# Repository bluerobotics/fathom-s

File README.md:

# Fathom-S

The Fathom Tether Boards are part of Blue Robotics' *Fathom Tether*. These boards provide interfaces and functionality for the communication methods used with the tether. With the Fathom tether, it is quick and easy to get up and running and interface with your ROV or other application.

The schematic and board layout are designed in EagleCAD.

Please see the [Blue Robotics Fathom-S Documentation Page](http://docs.bluerobotics.com/fathom-s/) for more information.

## License

The Fathom Serial Hardware Design is released under the MIT License.

## Revision History

0.0 - Under development. Not fully functional.

0.1 - Second prototype. Not fully functional.

0.2 - Third prototype. First beta release - works great.

0.3 - Rev5, incorporating big changes from beta tests.

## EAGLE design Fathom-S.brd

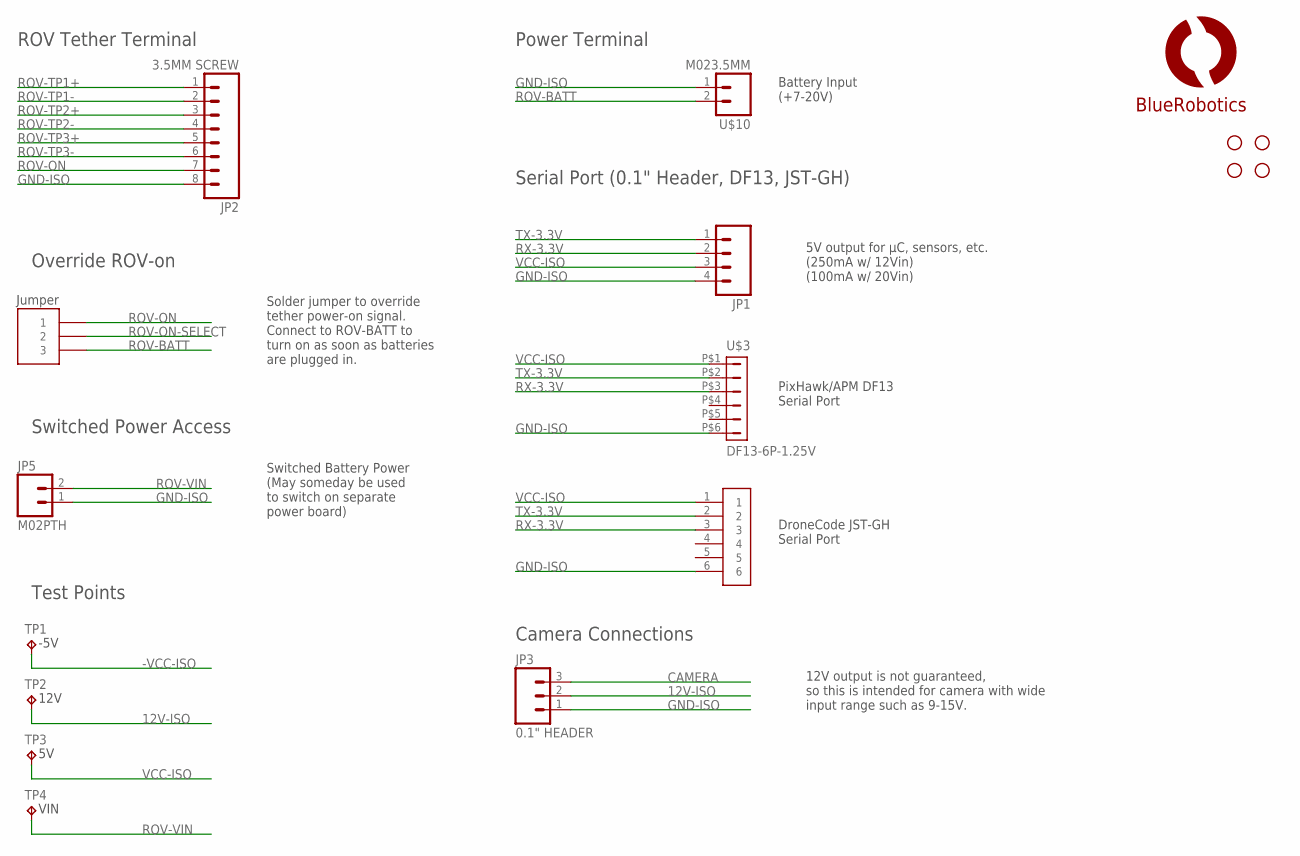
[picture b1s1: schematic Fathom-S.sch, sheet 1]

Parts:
JP1: M04PTH; 1X04
JP2: 3.5MM SCREW; SCREWTERMINAL-3.5MM-8
JP3: 0.1" HEADER; 1X03
JP5: M02PTH; 1X02
STANDOFF1, STANDOFF2, STANDOFF3, STANDOFF4: STAND-OFF
TP1: -5V; B1,27
TP2: 12V; B1,27
TP3: 5V; B1,27
TP4: VIN; B1,27
U$3: DF13-6P-1.25V; DF13C-6P-1.25V
U$4: LOGOFULL-M; BR-FULL-LOGO-MEDIUM
U$10: M023.5MM; SCREWTERMINAL-3.5MM-2
U$11: JST-GH-6TOP-ENTRY; JST-GH-TOP-6
U$13: HEADER-33MM; HEADER-2MM-3POS

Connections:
12V-ISO: JP3.2, TP2.TP; also elsewhere on the board
-VCC-ISO: TP1.TP; also elsewhere on the board
CAMERA: JP3.3; also elsewhere on the board
GND-ISO: JP1.4, JP2.8, JP3.1, JP5.1, U$3.P$6 (6), U$10.1, U$11.6; also elsewhere on the board
ROV-BATT: U$10.2, U$13.P$3 (3); also elsewhere on the board
ROV-ON: JP2.7, U$13.P$1 (1)
ROV-ON-SELECT: U$13.P$2 (2); also elsewhere on the board
ROV-TP1+: JP2.1; also elsewhere on the board
ROV-TP1-: JP2.2; also elsewhere on the board
ROV-TP2+: JP2.3; also elsewhere on the board
ROV-TP2-: JP2.4; also elsewhere on the board
ROV-TP3+: JP2.5; also elsewhere on the board
ROV-TP3-: JP2.6; also elsewhere on the board
ROV-VIN: JP5.2, TP4.TP; also elsewhere on the board
RX-3.3V: JP1.2, U$3.P$3 (3), U$11.3; also elsewhere on the board
TX-3.3V: JP1.1, U$3.P$2 (2), U$11.2; also elsewhere on the board
VCC-ISO: JP1.3, TP3.TP, U$3.P$1 (1), U$11.1; also elsewhere on the board

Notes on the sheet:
ROV Tether Terminal
Power Terminal
Camera Connections
Serial Port (0.1" Header, DF13, JST-GH)
Solder jumper to override tether power-on signal. Connect to ROV-BATT to turn on as soon as batteries are plugged in.
Override ROV-on
Battery Input (+7-20V)
5V output for µC, sensors, etc. (250mA w/ 12Vin) (100mA w/ 20Vin)
12V output is not guaranteed, so this is intended for camera with wide input range such as 9-15V.
Jumper
DroneCode JST-GH Serial Port
PixHawk/APM DF13 Serial Port
Switched Battery Power (May someday be used to switch on separate power board)
Switched Power Access
Test Points

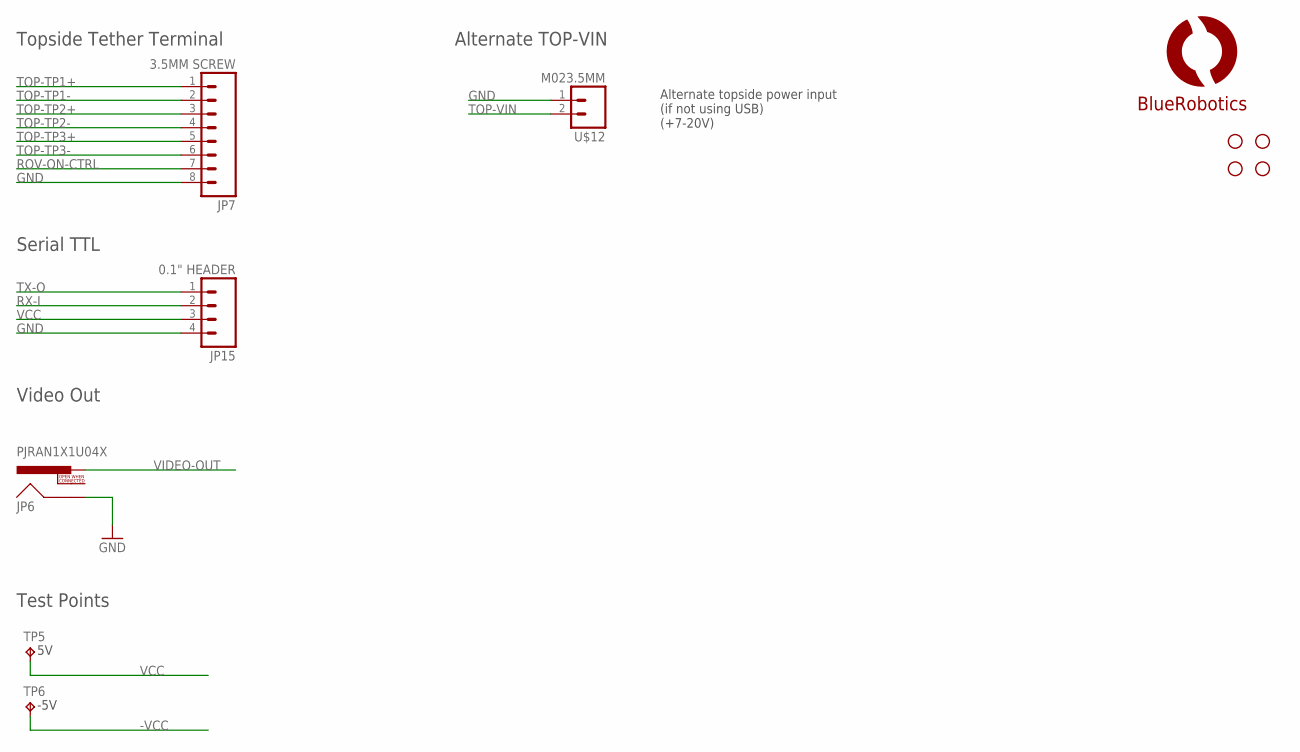
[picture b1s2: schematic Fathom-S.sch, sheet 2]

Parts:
JP6: PJRAN1X1U04X; RCA
JP7: 3.5MM SCREW; SCREWTERMINAL-3.5MM-8
JP15: 0.1" HEADER; 1X04
STANDOFF5, STANDOFF6, STANDOFF7, STANDOFF8: STAND-OFF
TP5: 5V; B1,27
TP6: -5V; B1,27
U$5: LOGOBR-LOGO-MS-COPPER; BR-LOGO-MEDIUM-SMALL-COPPER
U$12: M023.5MM; SCREWTERMINAL-3.5MM-2

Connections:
-VCC: TP6.TP; also elsewhere on the board
GND: JP6.SHELL, JP7.8, JP15.4, U$12.1; also elsewhere on the board
ROV-ON-CTRL: JP7.7; also elsewhere on the board
RX-I: JP15.2; also elsewhere on the board
TOP-TP1+: JP7.1; also elsewhere on the board
TOP-TP1-: JP7.2; also elsewhere on the board
TOP-TP2+: JP7.3; also elsewhere on the board
TOP-TP2-: JP7.4; also elsewhere on the board
TOP-TP3+: JP7.5; also elsewhere on the board
TOP-TP3-: JP7.6; also elsewhere on the board
TOP-VIN: U$12.2; also elsewhere on the board
TX-O: JP15.1; also elsewhere on the board
VCC: JP15.3, TP5.TP; also elsewhere on the board
VIDEO-OUT: JP6.PIN; also elsewhere on the board

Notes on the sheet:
Topside Tether Terminal
Alternate TOP-VIN
Video Out
Serial TTL
Alternate topside power input (if not using USB) (+7-20V)
Test Points

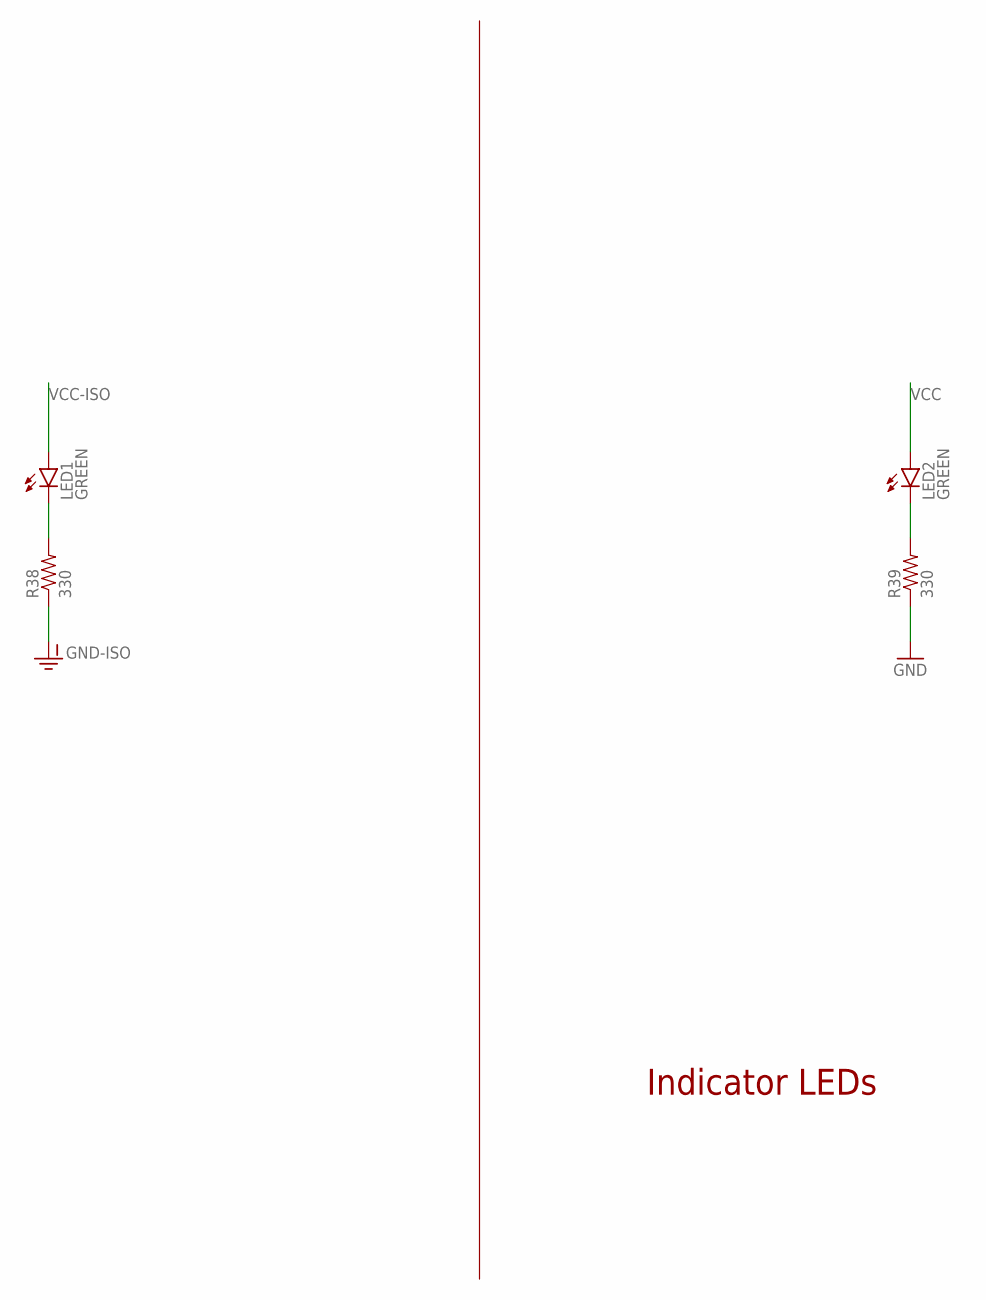
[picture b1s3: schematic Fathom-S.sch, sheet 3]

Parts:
LED1, LED2: GREEN; LED-0603
R38, R39: 330; 0603-RES

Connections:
GND: R39.1; also elsewhere on the board
GND-ISO: R38.1; also elsewhere on the board
unnamed: LED1.C, R38.2
unnamed: LED2.C, R39.2
VCC: LED2.A; also elsewhere on the board
VCC-ISO: LED1.A; also elsewhere on the board

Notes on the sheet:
Indicator LEDs

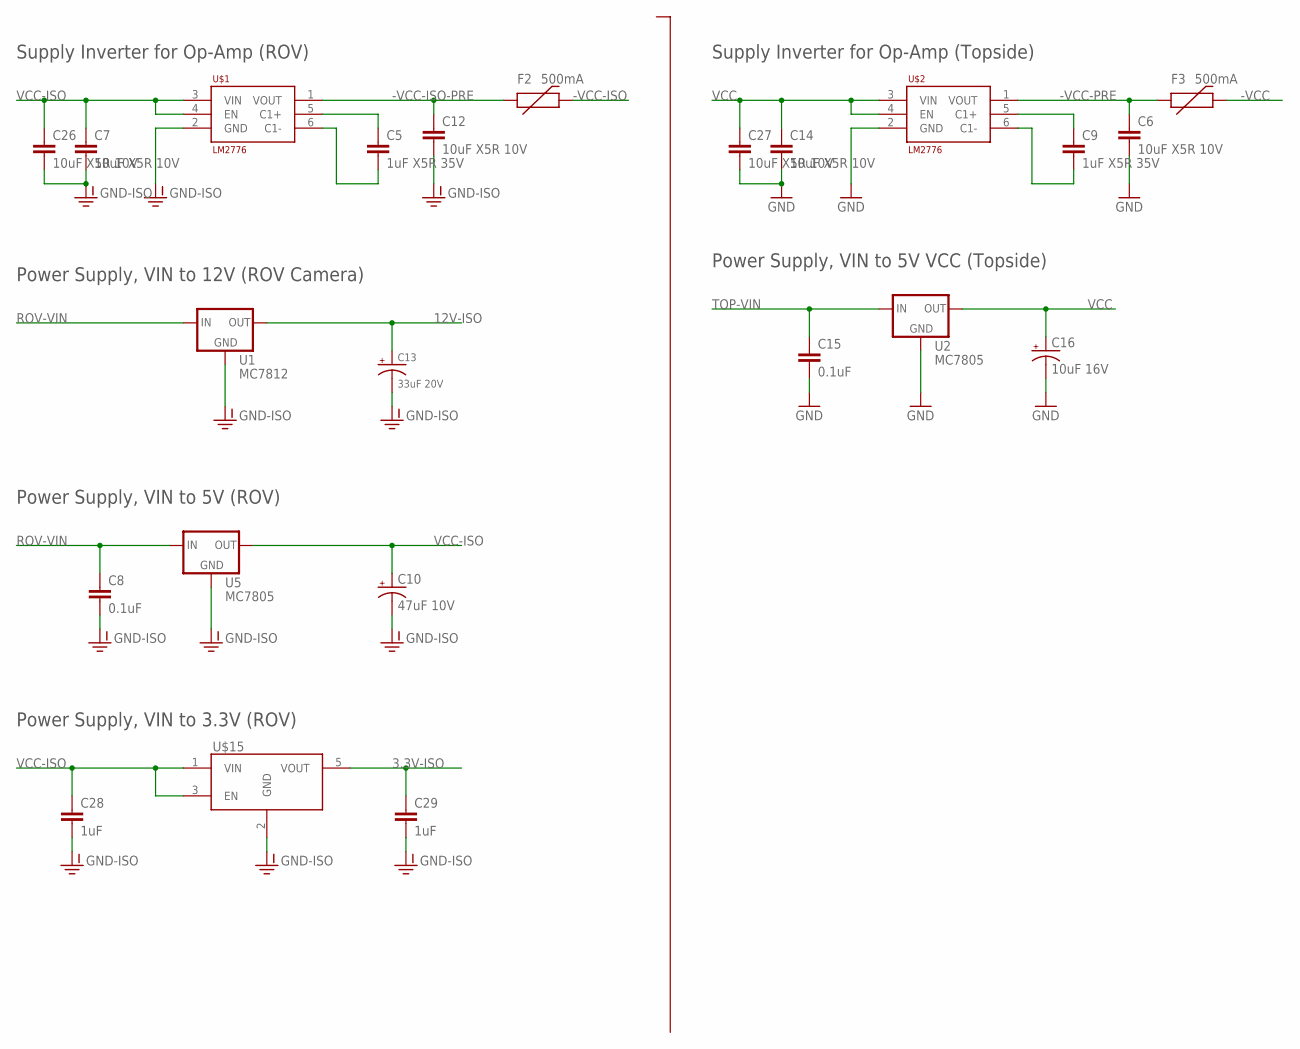
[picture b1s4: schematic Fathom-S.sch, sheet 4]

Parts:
C5, C9: 1uF X5R 35V; 0603-CAP
C6, C7, C12, C14, C26, C27: 10uF X5R 10V; 0805
C8, C15: 0.1uF; 0603-CAP
C10: 47uF 10V; EIA3528
C13: 33uF 20V; C2413
C16: 10uF 16V; EIA3216
C28, C29: 1uF; 0603-CAP
F2, F3: 500mA; 0603
U1: MC7812; DPAK
U2, U5: MC7805; DPAK
U$1, U$2: LM2776; SOT-23-6
U$15: VREG-MIC5365; SC70-5L

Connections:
3.3V-ISO: C29.1, U$15.5 (VOUT); also elsewhere on the board
12V-ISO: C13.+, U1.3 (OUT); also elsewhere on the board
-VCC: F3.2; also elsewhere on the board
-VCC-ISO: F2.2; also elsewhere on the board
-VCC-ISO-PRE: C12.1, F2.1, U$1.1 (VOUT)
-VCC-PRE: C6.1, F3.1, U$2.1 (VOUT)
GND: C6.2, C14.2, C15.2, C16.C (-), C27.2, U2.4 (GND), U$2.2 (GND); also elsewhere on the board
GND-ISO: C7.2, C8.2, C10.C (-), C12.2, C13.-, C26.2, C28.2, C29.2, U1.4 (GND), U5.4 (GND), U$1.2 (GND), U$15.2 (GND); also elsewhere on the board
unnamed: C9.1, U$2.5 (C1+)
unnamed: C9.2, U$2.6 (C1-)
unnamed: C5.1, U$1.5 (C1+)
unnamed: C5.2, U$1.6 (C1-)
ROV-VIN: C8.1, U1.1 (IN), U5.1 (IN); also elsewhere on the board
TOP-VIN: C15.1, U2.1 (IN); also elsewhere on the board
VCC: C14.1, C16.A (+), C27.1, U2.3 (OUT), U$2.3 (VIN), U$2.4 (EN); also elsewhere on the board
VCC-ISO: C7.1, C10.A (+), C26.1, C28.1, U5.3 (OUT), U$1.3 (VIN), U$1.4 (EN), U$15.1 (VIN), U$15.3 (EN); also elsewhere on the board

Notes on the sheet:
Supply Inverter for Op-Amp (ROV)
Supply Inverter for Op-Amp (Topside)
Power Supply, VIN to 12V (ROV Camera)
Power Supply, VIN to 5V (ROV)
Power Supply, VIN to 5V VCC (Topside)
Power Supply, VIN to 3.3V (ROV)

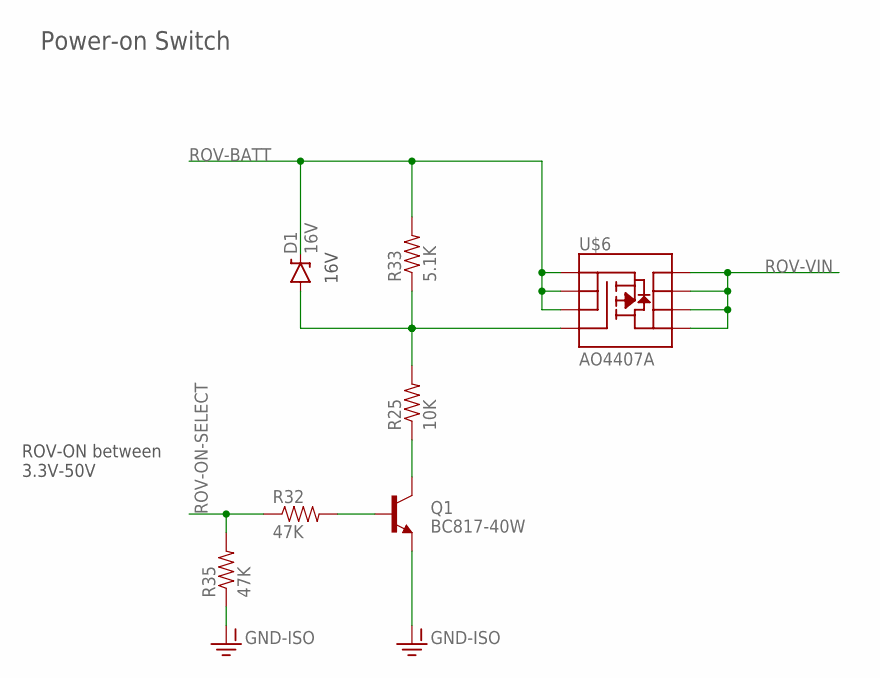
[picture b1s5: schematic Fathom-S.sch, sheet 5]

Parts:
D1: 16V; SOD-323
Q1: BC817-40W; SOT23
R25: 10K; 0603-RES
R32, R35: 47K; 0603-RES
R33: 5.1K; 0603-RES
U$6: AO4407A; SO08

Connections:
GND-ISO: Q1.2 (E), R35.1; also elsewhere on the board
unnamed: Q1.1 (B), R32.2
unnamed: D1.A, R25.2, R33.1, U$6.4 (G)
unnamed: Q1.3 (C), R25.1
ROV-BATT: D1.C, R33.2, U$6.1 (S), U$6.2 (S), U$6.3 (S); also elsewhere on the board
ROV-ON-SELECT: R32.1, R35.2; also elsewhere on the board
ROV-VIN: U$6.5 (D), U$6.6 (D), U$6.7 (D), U$6.8 (D); also elsewhere on the board

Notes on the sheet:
Power-on Switch
ROV-ON between 3.3V-50V
16V

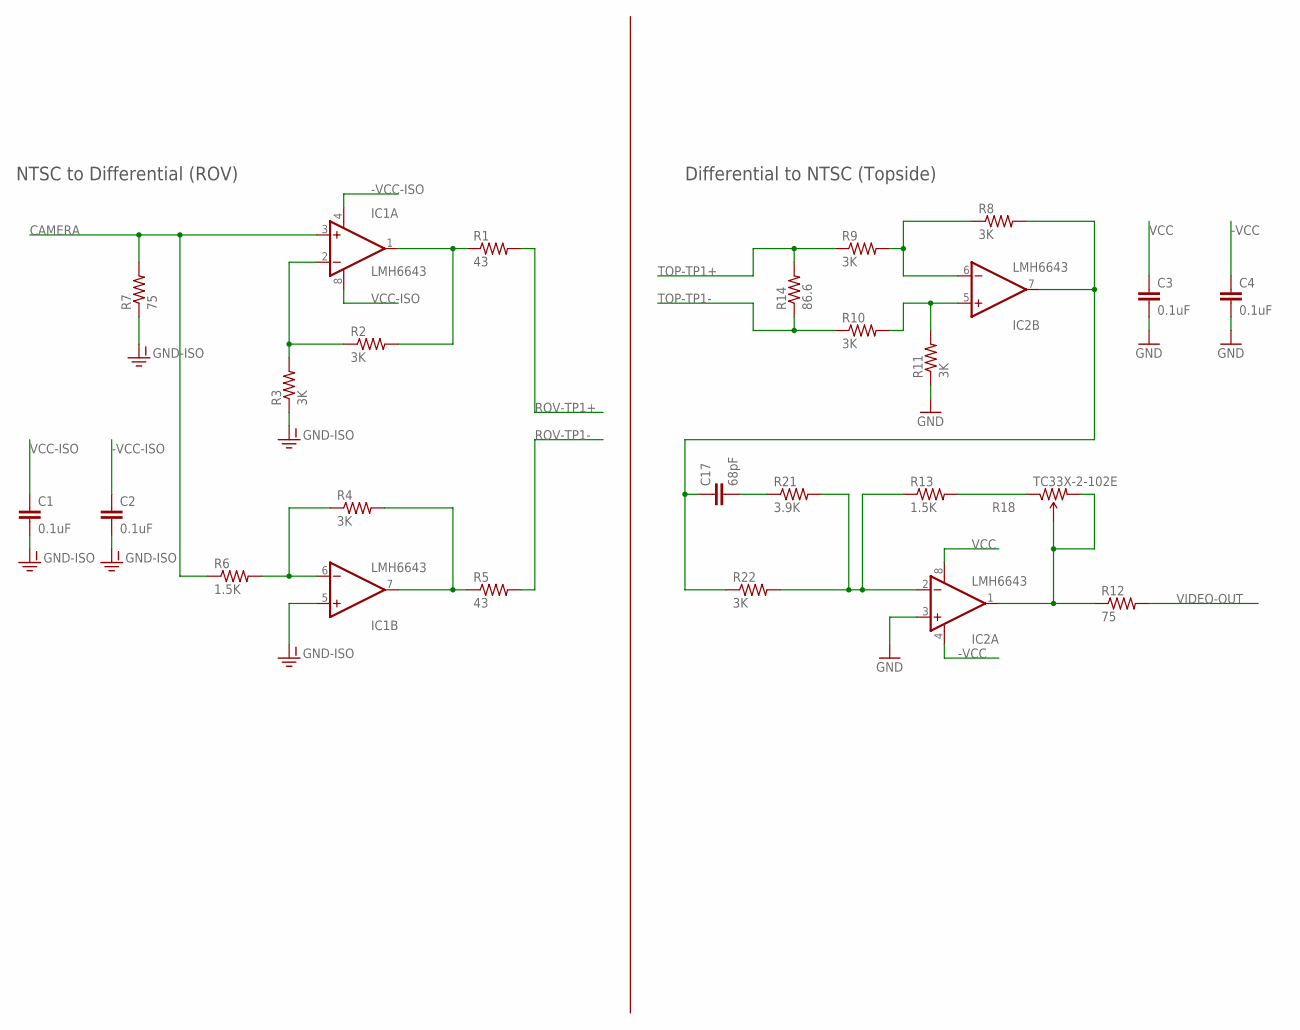
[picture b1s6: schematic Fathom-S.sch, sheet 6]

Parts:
C1, C2, C3, C4: 0.1uF; 0603-CAP
C17: 68pF; 0603-CAP
IC1, IC2: LMH6643; MSOP8
R1, R5: 43; 0603-RES
R2, R3, R4, R8, R9, R10, R11, R22: 3K; 0603-RES
R6, R13: 1.5K; 0603-RES
R7, R12: 75; 0603-RES
R14: 86.6; 0603-RES
R18: TC33X-2-102E; TRIMPOT_TC33
R21: 3.9K; 0603-RES

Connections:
-VCC: C4.1, IC2.4 (V-); also elsewhere on the board
-VCC-ISO: C2.1, IC1.4 (V-); also elsewhere on the board
CAMERA: IC1.3 (+IN), R6.1, R7.2; also elsewhere on the board
GND: C3.2, C4.2, IC2.3 (+IN), R11.1; also elsewhere on the board
GND-ISO: C1.2, C2.2, IC1.5 (+IN), R3.1, R7.1; also elsewhere on the board
unnamed: IC1.1 (OUT), R1.1, R2.2
unnamed: IC1.7 (OUT), R4.2, R5.1
unnamed: IC1.2 (-IN), R2.1, R3.2
unnamed: IC1.6 (-IN), R4.1, R6.2
unnamed: IC2.5 (+IN), R10.2, R11.2
unnamed: IC2.6 (-IN), R8.1, R9.2
unnamed: R13.2, R18.1 (CCW)
unnamed: C17.1, IC2.7 (OUT), R8.2, R22.1
unnamed: IC2.2 (-IN), R13.1, R21.2, R22.2
unnamed: C17.2, R21.1
unnamed: IC2.1 (OUT), R12.1, R18.2 (WIPER), R18.3 (CW)
ROV-TP1+: R1.2; also elsewhere on the board
ROV-TP1-: R5.2; also elsewhere on the board
TOP-TP1+: R9.1, R14.2; also elsewhere on the board
TOP-TP1-: R10.1, R14.1; also elsewhere on the board
VCC: C3.1, IC2.8 (V+); also elsewhere on the board
VCC-ISO: C1.1, IC1.8 (V+); also elsewhere on the board
VIDEO-OUT: R12.2; also elsewhere on the board

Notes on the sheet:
NTSC to Differential (ROV)
Differential to NTSC (Topside)

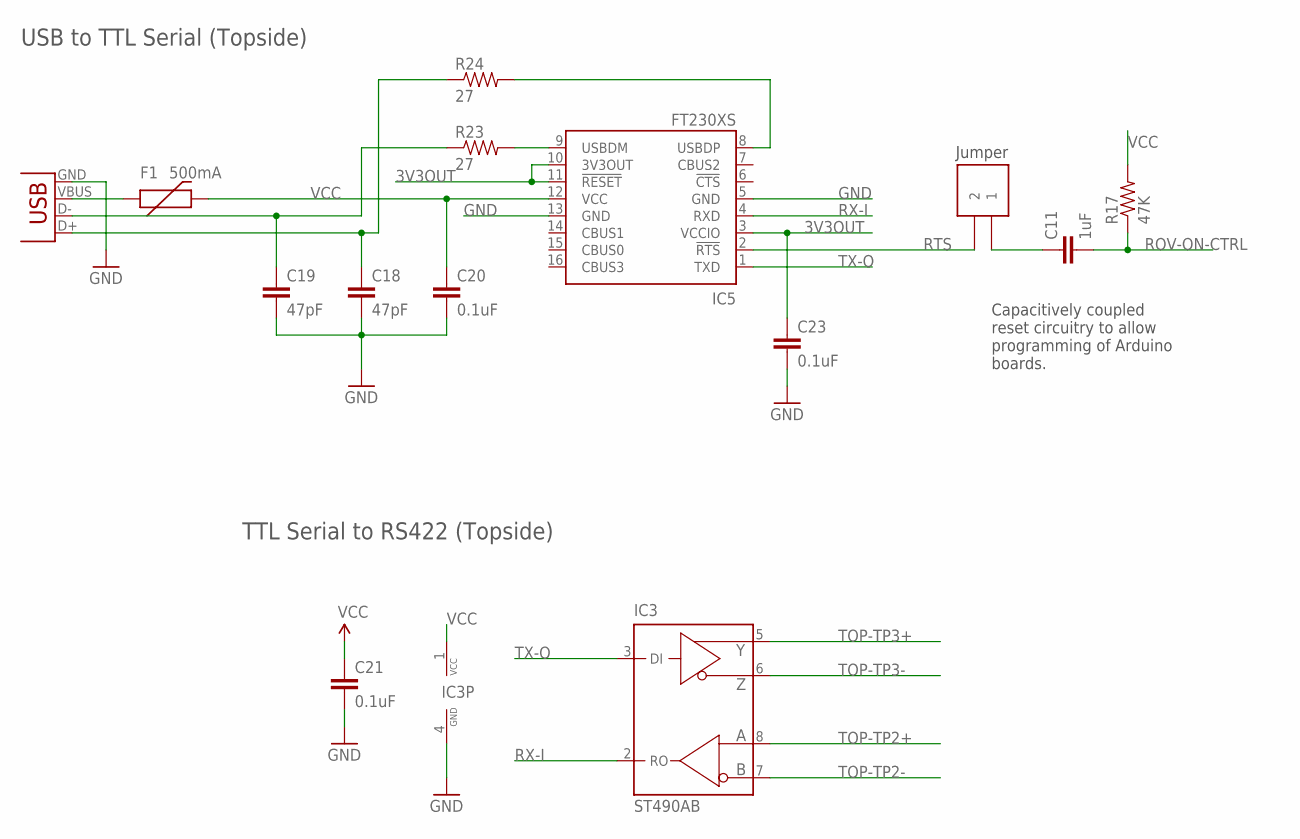
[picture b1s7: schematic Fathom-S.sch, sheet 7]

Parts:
C11: 1uF; 0603-CAP
C18, C19: 47pF; 0603-CAP
C20, C21, C23: 0.1uF; 0603-CAP
F1: 500mA; 0603
IC3: ST490AB; SO08
IC5: FT230XS; SSOP16
R17: 47K; 0603-RES
R23, R24: 27; 0603-RES
U$16: HEADER-22MM; HEADER-2MM-2POS
X2: USBSMD; USB-MINIB

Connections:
3V3OUT: C23.1, IC5.3 (VCCIO), IC5.10 (3V3OUT), IC5.11 (!RESET)
GND: C18.2, C19.2, C20.2, C21.2, C23.2, IC3.4 (GND), IC5.5 (GND), IC5.13 (GND), X2.GND; also elsewhere on the board
unnamed: C11.1, U$16.P$1 (1)
unnamed: C19.1, R23.1, X2.D-
unnamed: C18.1, R24.1, X2.D+
unnamed: F1.1, X2.VBUS
unnamed: IC5.8 (USBDP), R24.2
unnamed: IC5.9 (USBDM), R23.2
ROV-ON-CTRL: C11.2, R17.1; also elsewhere on the board
RTS: IC5.2 (!RTS), U$16.P$2 (2)
RX-I: IC3.2 (RO), IC5.4 (RXD); also elsewhere on the board
TOP-TP2+: IC3.8 (A); also elsewhere on the board
TOP-TP2-: IC3.7 (B); also elsewhere on the board
TOP-TP3+: IC3.5 (Y); also elsewhere on the board
TOP-TP3-: IC3.6 (Z); also elsewhere on the board
TX-O: IC3.3 (DI), IC5.1 (TXD); also elsewhere on the board
VCC: C20.1, C21.1, F1.2, IC3.1 (VCC), IC5.12 (VCC), R17.2; also elsewhere on the board

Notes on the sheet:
USB to TTL Serial (Topside)
TTL Serial to RS422 (Topside)
Capacitively coupled reset circuitry to allow programming of Arduino boards.
Jumper

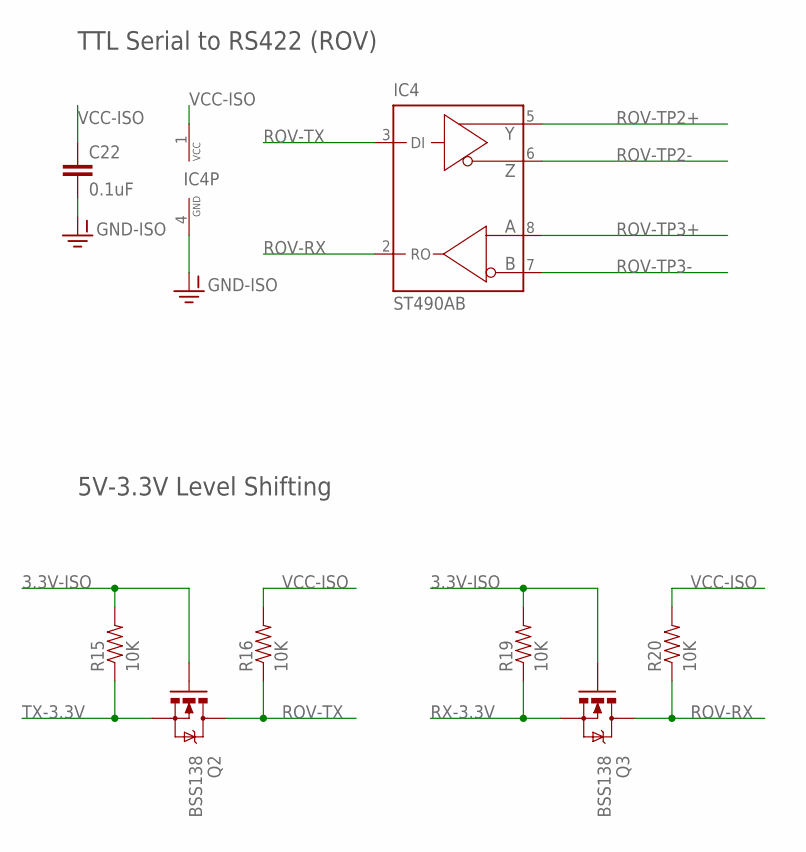
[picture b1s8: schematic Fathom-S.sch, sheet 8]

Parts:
C22: 0.1uF; 0603-CAP
IC4: ST490AB; SO08
Q2, Q3: BSS138; SOT23
R15, R16, R19, R20: 10K; 0603-RES

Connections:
3.3V-ISO: Q2.1 (G), Q3.1 (G), R15.2, R19.2; also elsewhere on the board
GND-ISO: C22.2, IC4.4 (GND); also elsewhere on the board
ROV-RX: IC4.2 (RO), Q3.3 (D), R20.1
ROV-TP2+: IC4.5 (Y); also elsewhere on the board
ROV-TP2-: IC4.6 (Z); also elsewhere on the board
ROV-TP3+: IC4.8 (A); also elsewhere on the board
ROV-TP3-: IC4.7 (B); also elsewhere on the board
ROV-TX: IC4.3 (DI), Q2.3 (D), R16.1
RX-3.3V: Q3.2 (S), R19.1; also elsewhere on the board
TX-3.3V: Q2.2 (S), R15.1; also elsewhere on the board
VCC-ISO: C22.1, IC4.1 (VCC), R16.2, R20.2; also elsewhere on the board

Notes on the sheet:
TTL Serial to RS422 (ROV)
5V-3.3V Level Shifting

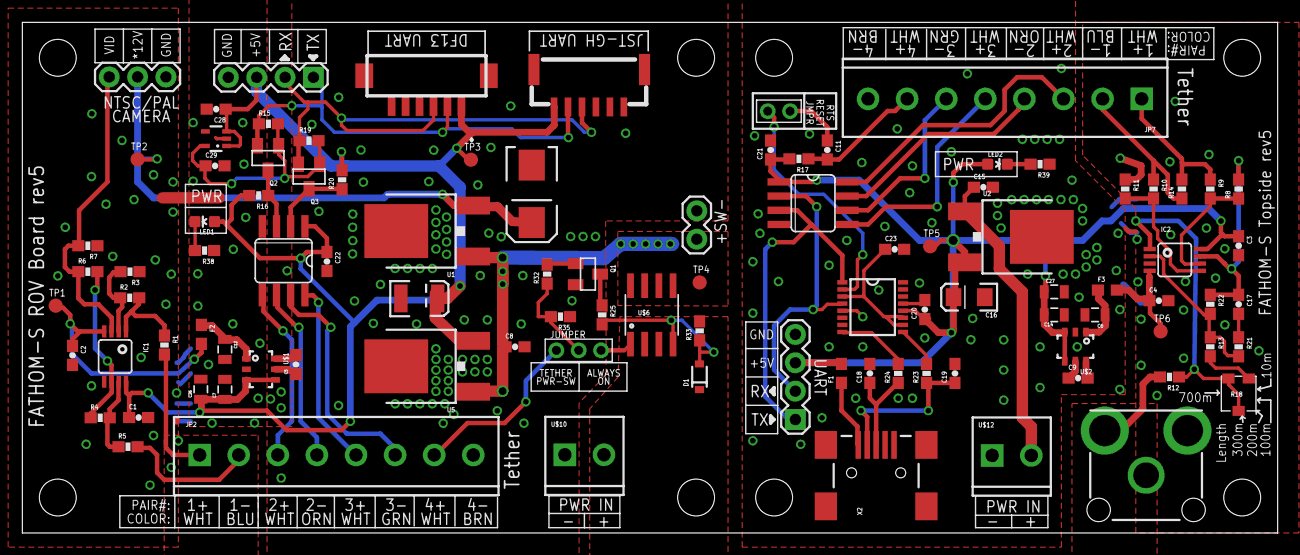
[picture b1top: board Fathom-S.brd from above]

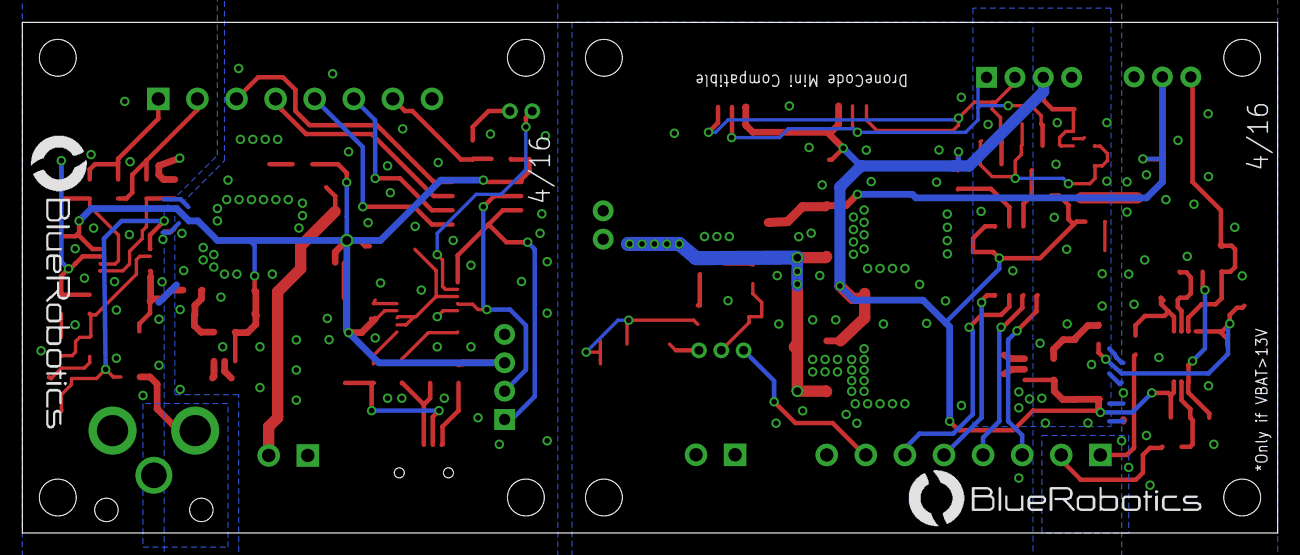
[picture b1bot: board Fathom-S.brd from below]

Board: 2 copper layers, 112.4 x 45.7 mm, 110 parts (2 on the bottom side), 64 nets.

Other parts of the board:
U$7: LOGOFULL-M; BR-FULL-LOGO-MEDIUM
U$9: LOGOBR-LOGO-MS; BR-LOGO-MEDIUM-SMALL-COPPER

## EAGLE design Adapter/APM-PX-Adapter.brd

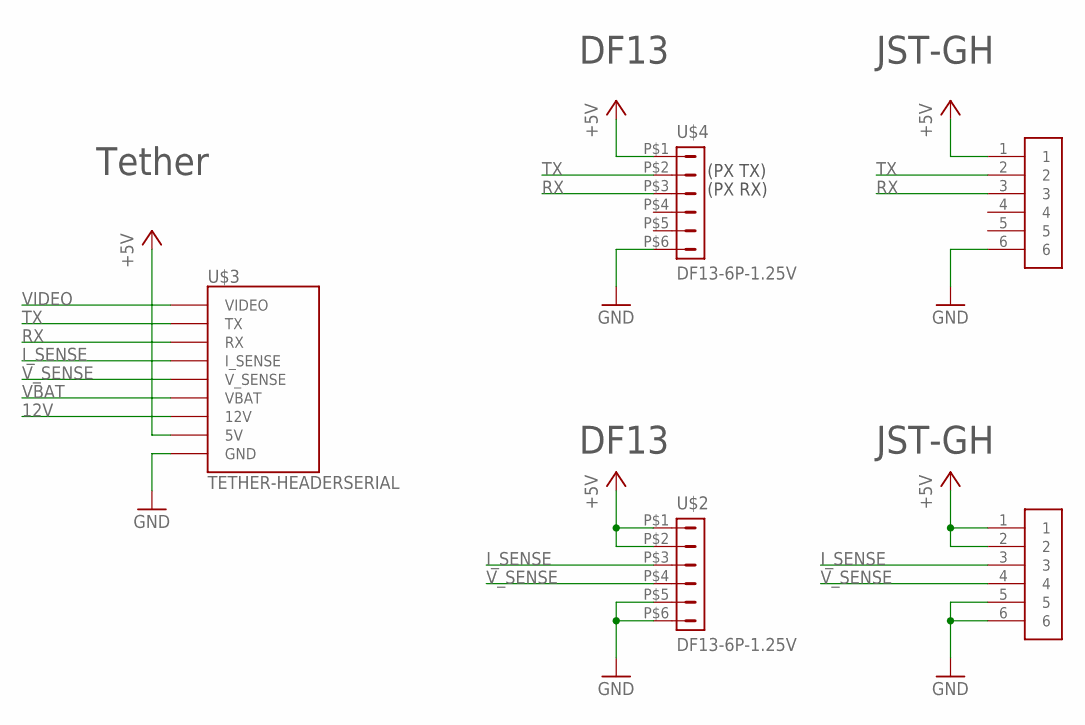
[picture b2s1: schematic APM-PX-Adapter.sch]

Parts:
U$1, U$5: JST-GH-6TOP-ENTRY; JST-GH-TOP-6
U$2, U$4: DF13-6P-1.25V; DF13C-6P-1.25V
U$3: TETHER-HEADERSERIAL; TETHER-HEADER-2X7

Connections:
12V: U$3.12V
+5V: U$1.1, U$2.P$1 (1), U$2.P$2 (2), U$3.5V, U$4.P$1 (1), U$5.1, U$5.2
GND: U$1.6, U$2.P$5 (5), U$2.P$6 (6), U$3.GND0 (GND), U$3.GND1 (GND), U$3.GND2 (GND), U$4.P$6 (6), U$5.5, U$5.6
I_SENSE: U$2.P$3 (3), U$3.I_SENSE, U$5.3
RX: U$1.3, U$3.RX, U$4.P$3 (3)
TX: U$1.2, U$3.TX, U$4.P$2 (2)
VBAT: U$3.VBAT
VIDEO: U$3.VIDEO
V_SENSE: U$2.P$4 (4), U$3.V_SENSE, U$5.4

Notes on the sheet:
(PX TX)
(PX RX)
Tether
DF13
JST-GH

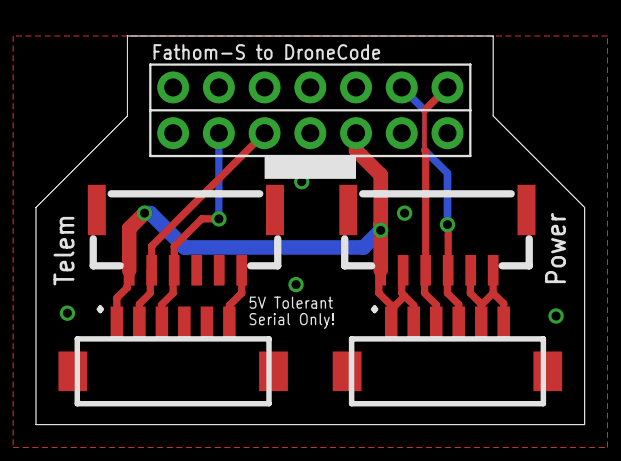
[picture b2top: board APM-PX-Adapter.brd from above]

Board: 2 copper layers, 30.5 x 21.6 mm, 5 parts (0 on the bottom side), 6 nets.

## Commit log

2015-10-11 Initial commit, already pretty fully designed, but not yet produced or tested.
2015-10-12 Increased termination resistor size appropriately for RS485. Hopefully we can get by without using these eventually.
2015-10-12 Updated tether ribbon header size and pinout.
2015-10-12 Adjusted silkscreen text.
2015-10-18 Minor update to readme.
2015-10-18 Initialized LX200V20 test branch.
2015-10-18 Added schematic for test module.
2015-11-01 Lots of changes based on testing of first prototype. Fixed regulators, removed RX/TX leds, added RTS reset, changed negative supply capacitors.
2015-11-02 Updated schematic frames and changed references from 485 to 422.
2015-11-02 Changed file names.
2015-11-05 Changed lm2776 components to match datasheet and hopefully fix our issues.
2015-11-05 Layout 'typos' fixed.
2015-11-19 Redid the layout for the video amplifiers and supply inverters to help fix recent issues. There is now an analog ground plane. LM2776 are laid out almost identical to the eval board.
2015-11-19 Fixed a few minor ground issues.
2015-11-20 Fixed a bunch of routing issues, added more ground vias, changed ground planes a bit.
2015-11-21 Changed the op-amp package because the MSOPs are much cheaper for some reason.
2015-11-21 Minor changes to readme and silkscreen.
2015-11-23 Yet more layout changes and added ferrite beads to the -5V outputs for better noise rejection.
2015-11-24 Fixed a few more layout issues and connected the pot wiper to open end for safety.
2015-11-24 Moved components slightly to move pot up.
2015-11-24 Minor fix.
2015-11-24 Fixed an unnecessarily long 12V trace.
2015-11-24 Added revision to readme.
2015-12-16 Removed soldermask from vias.
2015-12-16 Adding APM/Pixhawk adapter. This has level shifters and stuff, but apparently the Pixhawk serial port is 5V tolerant so I will be removing them and making it simple.
2015-12-16 Removed level shifting and switch to all through hole components. Ordering a prototype.
2015-12-18 Change resistor value to fix RTS reset and added more thermal vias for regulators.
2015-12-23 Changed jumpers from solder to headers. This rev4 and the beta boards will be ordered from this commit.
2016-01-27 Readme updates.
2016-04-16 Updates to adapter board.
2016-04-16 Massive revision to simplify and make easier to use. Added DroneCode connectors, removed excessive stuff, and removed power switching.
2016-04-16 Updated README for rev5.
2016-04-18 Change 12V output capacitor size.
2016-04-20 Switch to FET based level shifting for 5V tolerance.
2016-04-25 Further updates to Rev5. First production run.
2016-05-16 Updated files before release.
2016-05-16 Remove irrelevant adapter boards.
2016-05-18 Update specs.

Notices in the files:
parts and their libraries:
SparkFun-Passives: Licensing: Creative Commons ShareAlike 4.0 International - https://creativecommons.org/licenses/by-sa/4.0
